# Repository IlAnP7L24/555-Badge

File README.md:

# 2-LED-Badge
 PCB base for a 2-LED badge fully designed in KiCAD

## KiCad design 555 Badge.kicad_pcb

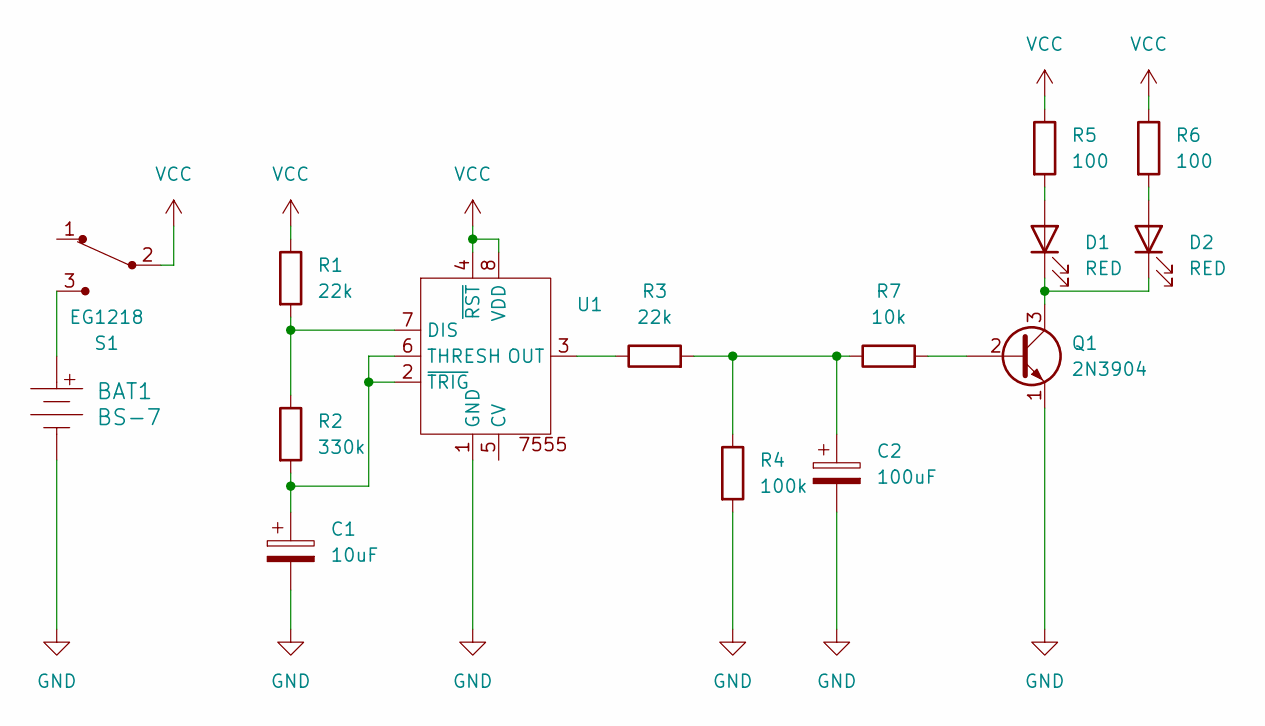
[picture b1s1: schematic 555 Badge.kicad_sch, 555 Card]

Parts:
BAT1: BS-7; Battery_Holder_Coin_2032_BS-7; MPN BS-7; Digi-Key_PN BS-7-ND
C1: 10uF; C_Radial_D5.0mm_H5.0mm_P2.00mm
C2: 100uF; C_Radial_D6.3mm_H5.0mm_P2.50mm
D1, D2: RED; LED_D3.0mm
Q1: 2N3904; TO-92-3
R1, R3: 22k; R_Axial_DIN0207_L6.3mm_D2.5mm_P7.62mm_Horizontal
R2: 330k; R_Axial_DIN0207_L6.3mm_D2.5mm_P7.62mm_Horizontal
R4: 100k; R_Axial_DIN0207_L6.3mm_D2.5mm_P7.62mm_Horizontal
R5, R6: 100; R_Axial_DIN0207_L6.3mm_D2.5mm_P7.62mm_Horizontal
R7: 10k; R_Axial_DIN0207_L6.3mm_D2.5mm_P7.62mm_Horizontal
S1: EG1218; Switch_Slide_11.6x4mm_EG1218; MPN EG1218; Digi-Key_PN EG1903-ND
U1: ICM7555-PDIP

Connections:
GND: BAT1.Neg, C1.2, C2.2, Q1.1 (E), R4.2, U1.1 (GND)
unnamed: BAT1.Pos, S1.3
unnamed: C2.1, R3.2, R4.1, R7.1
unnamed: D1.2 (A), R5.2
unnamed: D1.1 (K), D2.1 (K), Q1.3 (C)
unnamed: D2.2 (A), R6.2
unnamed: Q1.2 (B), R7.2
unnamed: R1.2, R2.1, U1.7 (DIS)
unnamed: R3.1, U1.3 (OUT)
unnamed: C1.1, R2.2, U1.2 (~TRIG), U1.6 (THRESH)
VCC: R1.1, R5.1, R6.1, S1.2, U1.4 (~RST), U1.8 (VDD)

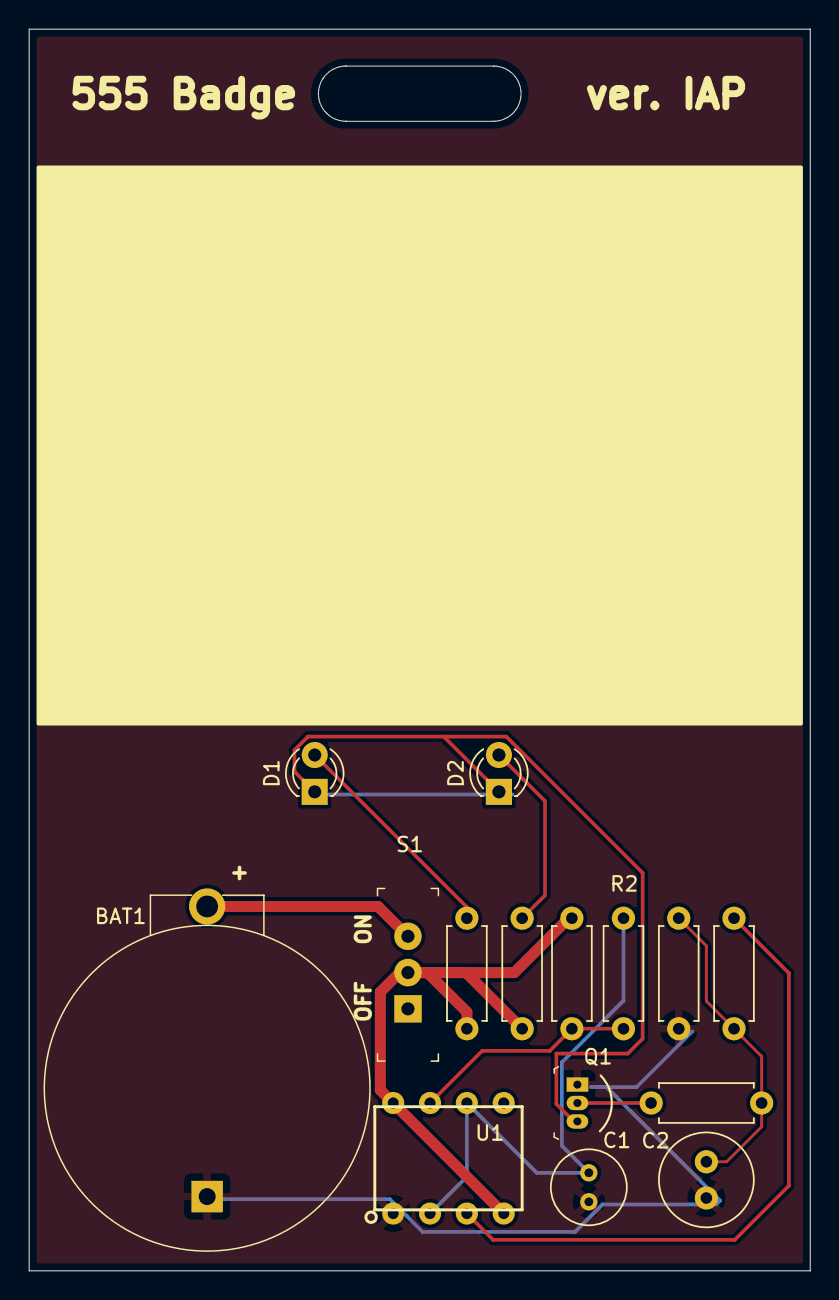
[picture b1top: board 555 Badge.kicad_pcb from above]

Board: 2 copper layers, 53.8 x 85.6 mm, 15 parts (0 on the bottom side), 11 nets.

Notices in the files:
555 Badge.kicad_pcb:
License: CC BY 4.0
